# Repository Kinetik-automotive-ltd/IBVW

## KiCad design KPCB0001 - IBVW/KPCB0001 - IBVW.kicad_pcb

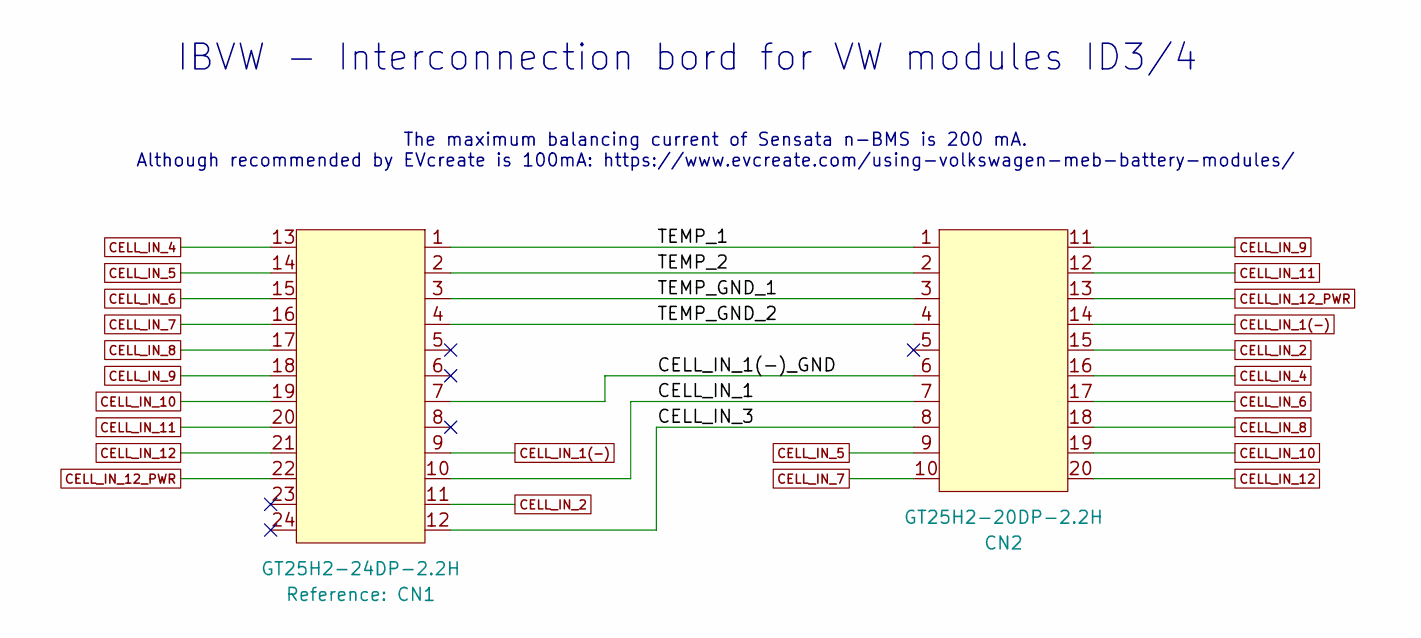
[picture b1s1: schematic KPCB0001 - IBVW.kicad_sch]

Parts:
CN1: GT25H2-24DP-2.2H; GT25H2-24DP-2.2H(99)
CN2: GT25H2-20DP-2.2H; GT25H2-20DP-2.2H(99)

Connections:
/CELL_IN_1: CN1.10, CN2.7
/CELL_IN_1(-)_GND: CN1.7, CN2.6
/CELL_IN_3: CN1.12, CN2.8
/TEMP_1: CN1.1, CN2.1
/TEMP_2: CN1.2, CN2.2
/TEMP_GND_1: CN1.3, CN2.3
/TEMP_GND_2: CN1.4, CN2.4
CELL_IN_1(-): CN1.9, CN2.14
CELL_IN_2: CN1.11, CN2.15
CELL_IN_4: CN1.13, CN2.16
CELL_IN_5: CN1.14, CN2.9
CELL_IN_6: CN1.15, CN2.17
CELL_IN_7: CN1.16, CN2.10
CELL_IN_8: CN1.17, CN2.18
CELL_IN_9: CN1.18, CN2.11
CELL_IN_10: CN1.19, CN2.19
CELL_IN_11: CN1.20, CN2.12
CELL_IN_12: CN1.21, CN2.20
CELL_IN_12_PWR: CN1.22, CN2.13

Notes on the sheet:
The maximum balancing current of Sensata n-BMS is 200 mA. Although recommended by EVcreate is 100mA: https://www.evcreate.com/using-volkswagen-meb-battery-modules/
IBVW - Interconnection bord for VW modules ID3/4

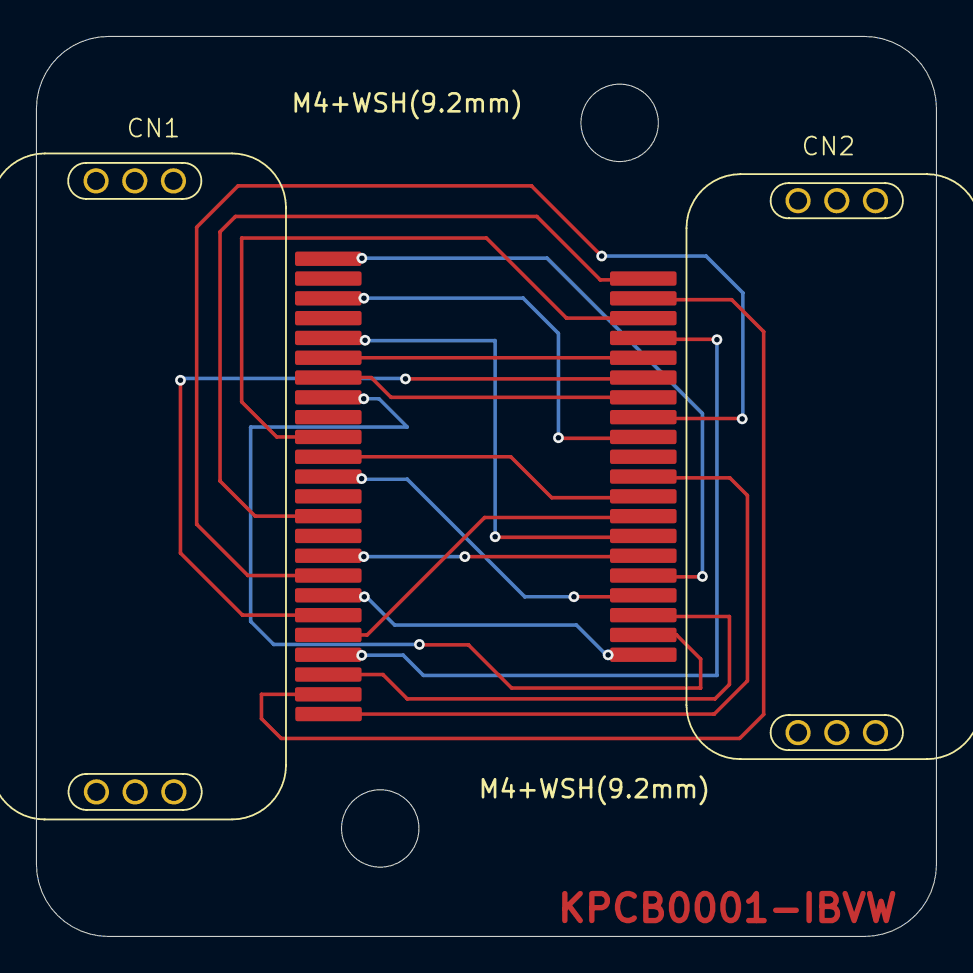
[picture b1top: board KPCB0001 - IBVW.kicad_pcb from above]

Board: 2 copper layers, 50.0 x 50.0 mm, 4 parts (0 on the bottom side), 19 nets.

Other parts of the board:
M4+WSH(9.2mm), M4+WSH(9.2mm)#2: MountingHole_4.3mm_M4

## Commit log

2025-07-28 Files for interconnection bord
    Interconnection board an all the files related and created with it
